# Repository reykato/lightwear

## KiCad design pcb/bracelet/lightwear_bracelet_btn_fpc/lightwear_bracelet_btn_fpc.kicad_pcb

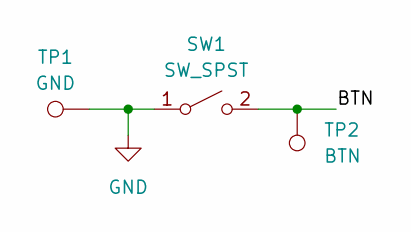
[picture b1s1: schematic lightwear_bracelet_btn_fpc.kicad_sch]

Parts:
SW1: SW_SPST; GT-TC155X-HXXXX-LX
TP1: GND; TestPoint_Pad_1.5x0.8mm_slim
TP2: BTN; TestPoint_Pad_1.5x0.8mm_slim

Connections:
/BTN: SW1.2 (B), TP2.1
GND: SW1.1 (A), TP1.1

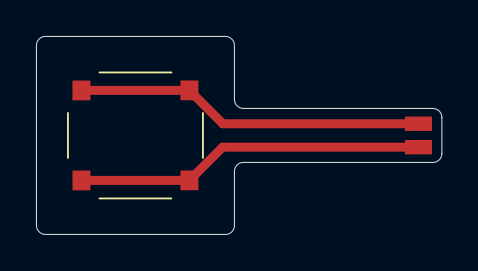
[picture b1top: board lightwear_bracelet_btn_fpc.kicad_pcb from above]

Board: 2 copper layers, 22.5 x 11.0 mm, 3 parts (0 on the bottom side), 2 nets.

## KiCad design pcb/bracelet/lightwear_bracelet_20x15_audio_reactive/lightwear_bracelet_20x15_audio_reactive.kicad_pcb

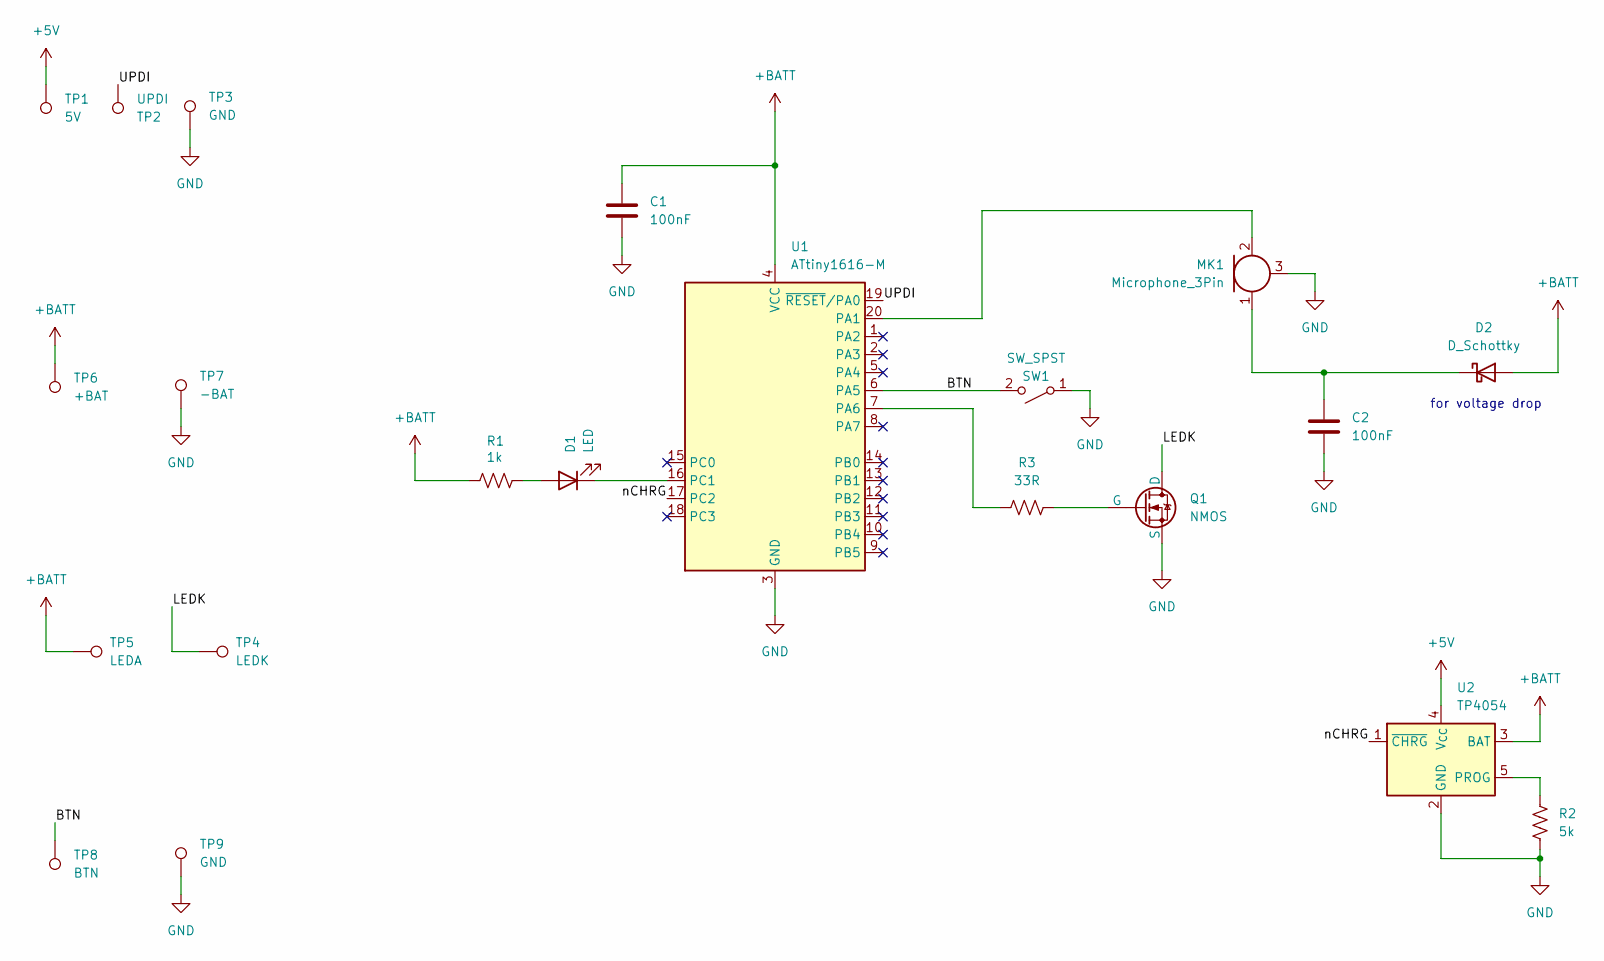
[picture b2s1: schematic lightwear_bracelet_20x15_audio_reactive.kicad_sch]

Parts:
C1, C2: 100nF; C_0402_1005Metric
D1: LED; LED_0603_1608Metric
D2: D_Schottky; SOT-23
MK1: Microphone_3Pin; MSM381ACB026
Q1: NMOS; SOT-23-MOSFET
R1: 1k; R_0402_1005Metric
R2: 5k; R_0402_1005Metric
R3: 33R; R_0402_1005Metric
SW1: SW_SPST; SW4_PTS815 SJM 250 SMTR LFS_CNK
TP1: 5V; TestPoint_Pad_D1.5mm
TP2: UPDI; TestPoint_Pad_D1.5mm
TP3: GND; TestPoint_Pad_D1.5mm
TP4: LEDK; TestPoint_Pad_2.0x1.2mm_slim
TP5: LEDA; TestPoint_Pad_2.0x1.2mm_slim
TP6: +BAT; TestPoint_Pad_Triangle
TP7: -BAT; TestPoint_Pad_Triangle
TP8: BTN; TestPoint_Pad_1.5x0.8mm_slim
TP9: GND; TestPoint_Pad_1.5x0.8mm_slim
U1: ATtiny1616-M; VQFN-20-1EP_3x3mm_P0.4mm_EP1.7x1.7mm
U2: TP4054; TSOT-23-5

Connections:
+5V: TP1.1, U2.4 (V_{CC})
+BATT: C1.1, D2.2 (A), R1.1, TP5.1, TP6.1, U1.4 (VCC), U2.3 (BAT)
/BTN: SW1.2 (B), TP8.1, U1.6 (PA5)
/LEDK: Q1.1 (D), TP4.1
/UPDI: TP2.1, U1.19 (~RESET/PA0)
/nCHRG: U1.17 (PC2), U2.1 (~CHRG)
GND: C1.2, C2.1, MK1.3 (GND), Q1.3 (S), R2.2, SW1.1 (A), TP3.1, TP7.1, TP9.1, U1.3 (GND), U1.21 (GND), U2.2 (GND)
unnamed: D1.2 (A), R1.2
unnamed: D1.1 (K), U1.16 (PC1)
unnamed: C2.2, D2.1 (K), MK1.1 (VDD)
unnamed: MK1.2 (OUT), U1.20 (PA1)
unnamed: Q1.2 (G), R3.2
unnamed: R3.1, U1.7 (PA6)
unnamed: R2.1, U2.5 (PROG)

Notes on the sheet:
for voltage drop

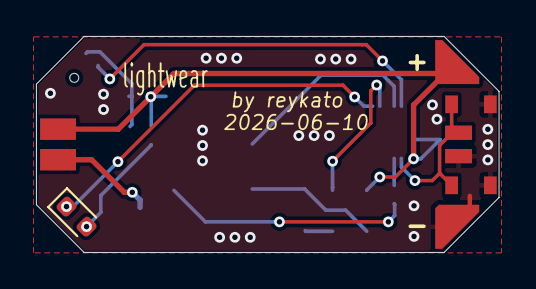
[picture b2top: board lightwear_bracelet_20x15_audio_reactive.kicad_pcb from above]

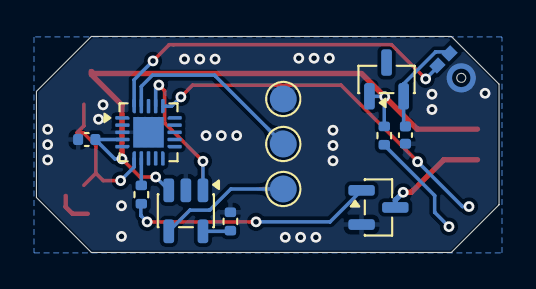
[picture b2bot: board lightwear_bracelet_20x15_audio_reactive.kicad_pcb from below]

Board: 2 copper layers, 25.7 x 12.0 mm, 21 parts (13 on the bottom side), 14 nets.

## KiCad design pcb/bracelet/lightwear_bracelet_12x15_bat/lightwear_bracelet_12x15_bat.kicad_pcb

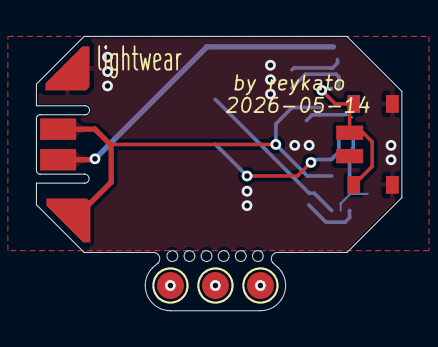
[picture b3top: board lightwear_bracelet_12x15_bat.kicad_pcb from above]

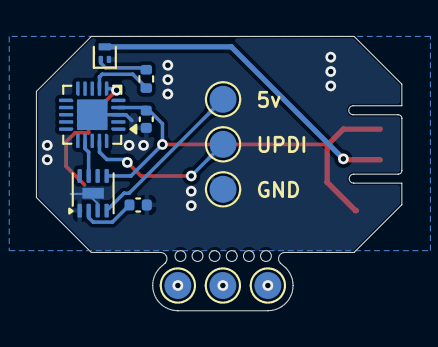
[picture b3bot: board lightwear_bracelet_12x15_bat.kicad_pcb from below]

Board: 2 copper layers, 20.3 x 15.2 mm, 22 parts (12 on the bottom side), 13 nets.

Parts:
C1: 100nF; C_0402_1005Metric
Q1: NMOS; SOT-883
R2: 22k; C_0402_1005Metric
R3: 33R; R_0402_1005Metric
SW1: SW_SPST; SW4_PTS815 SJM 250 SMTR LFS_CNK
TP1, TP2, TP3, TP4#2, TP5#2, TP6#2: TestPoint; TestPoint_Pad_D1.5mm
TP1#2: 5V; TestPoint_Pad_D1.5mm
TP2#2: UPDI; TestPoint_Pad_D1.5mm
TP3#2: GND; TestPoint_Pad_D1.5mm
TP4: LEDK; TestPoint_Pad_2.0x1.2mm_slim
TP5: LEDA; TestPoint_Pad_2.0x1.2mm_slim
TP6: +BAT; TestPoint_Pad_Triangle
TP7: -BAT; TestPoint_Pad_Triangle
TP8: BTN; TestPoint_Pad_1.5x0.8mm_slim
TP9: GND; TestPoint_Pad_1.5x0.8mm_slim
U1: ATtiny1616-M; VQFN-20-1EP_3x3mm_P0.4mm_EP1.7x1.7mm
U2: WB6058D; DFN-8-1EP_2x2mm_P0.5mm_EP0.6x1.2mm

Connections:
+5V: TP1#2.1, U2.4 (V_{CC})
+BATT: C1.1, TP5.1, TP6.1, U1.4 (VCC), U2.5 (BAT)
/BTN: SW1.2 (B), TP8.1, U1.6 (PA5)
/LEDK: Q1.3 (D), TP4.1
/UPDI: TP2#2.1, U1.19 (~RESET/PA0)
/nCHRG: U1.17 (PC2), U2.7 (~CHRG)
GND: C1.2, Q1.2 (S), R2.1, SW1.1 (A), TP3#2.1, TP7.1, TP9.1, U1.3 (GND), U1.21 (GND), U2.1 (TEMP), U2.3 (GND), U2.9 (BASE)
unnamed: Q1.1 (G), R3.2
unnamed: TP1.1, TP6#2.1
unnamed: TP2.1, TP5#2.1
unnamed: TP3.1, TP4#2.1
unnamed: R3.1, U1.7 (PA6)
unnamed: R2.2, U2.2 (ISET)

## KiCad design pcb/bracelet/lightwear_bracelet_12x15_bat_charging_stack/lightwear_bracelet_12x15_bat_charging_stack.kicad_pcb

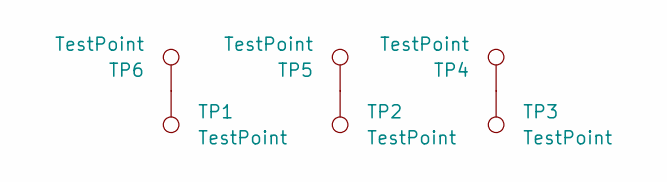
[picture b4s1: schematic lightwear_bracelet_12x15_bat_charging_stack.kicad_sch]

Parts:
TP1, TP2, TP3, TP4, TP5, TP6: TestPoint; TestPoint_Pad_D1.5mm

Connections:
unnamed: TP1.1, TP6.1
unnamed: TP2.1, TP5.1
unnamed: TP3.1, TP4.1

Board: 6 copper layers, 6 parts (3 on the bottom side), 3 nets, no tracks yet.

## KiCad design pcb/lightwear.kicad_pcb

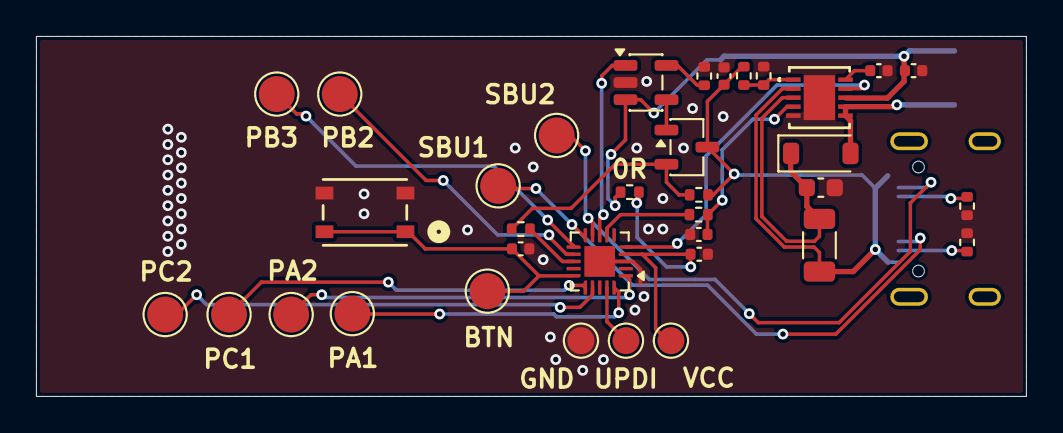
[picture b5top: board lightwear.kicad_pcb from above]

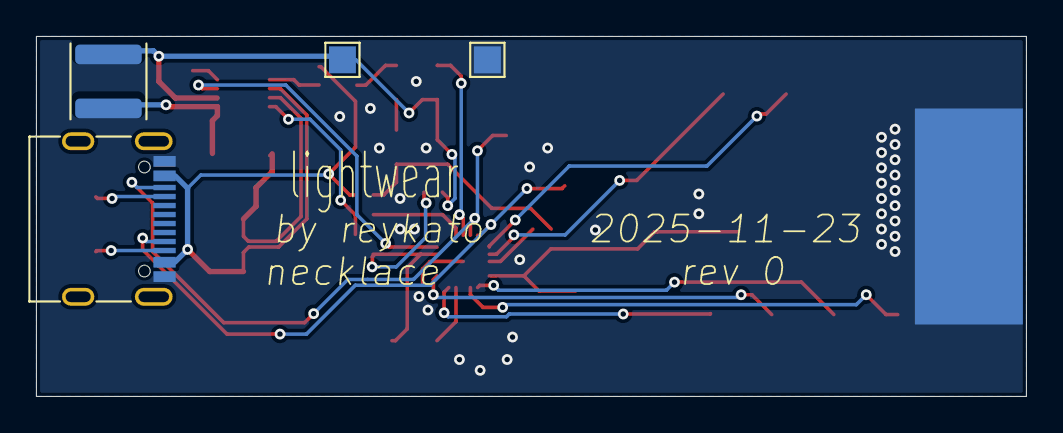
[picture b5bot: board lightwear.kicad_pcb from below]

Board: 2 copper layers, 55.0 x 20.0 mm, 40 parts (5 on the bottom side), 28 nets.

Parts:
C1, C4: 100nF; C_0402_1005Metric
C2: 1uF 35V; C_0603_1608Metric
C5: 2.2uF; C_0402_1005Metric
C6: 470nF; C_0402_1005Metric
C7: 4.7uF; C_0402_1005Metric
C8: 1uF 30V; C_0402_1005Metric
D1: D_Schottky 30V; D_SOD-123
J1: USB_C_Receptacle_USB2.0_16P; USB_C_Receptacle_G-Switch_GT-USB-7010ASV
L1: 4.7uH; L_Changjiang_FNR4030S
Q1: PMOS; SOT-23-3
R1: 33R; R_0402_1005Metric
R3, R4, R11: 5.1k; R_0402_1005Metric
R6: 0.05R; R_1206_3216Metric
R7: 100k 30V; R_0402_1005Metric
R8: 2k; R_0402_1005Metric
R9: 0R; R_0402_1005Metric
R10: 200k 30V; R_0402_1005Metric
R12: 10k 30V; R_0402_1005Metric
SW1: SW_SPST; SW4_PTS815 SJM 250 SMTR LFS_CNK
TP1: USB_SBU1; TestPoint_Pad_D2.0mm
TP2: BTN; TestPoint_Pad_D2.0mm
TP3: MCU_VCC; TestPoint_Pad_D1.5mm
TP4: UPDI; TestPoint_Pad_D1.5mm
TP5: GND; TestPoint_Pad_D1.5mm
TP6: +BATT; TestPoint_Pad_1.5x1.5mm
TP7: GND; TestPoint_Pad_1.5x1.5mm
TP8: PA1; TestPoint_Pad_D2.0mm
TP9: LEDK; TestPoint_Pad_6.0x12.0mm
TP10: PA2; TestPoint_Pad_D2.0mm
TP11: PB2; TestPoint_Pad_D2.0mm
TP12: PB3; TestPoint_Pad_D2.0mm
TP13: PC1; TestPoint_Pad_D2.0mm
TP14: PC2; TestPoint_Pad_D2.0mm
TP16: USB_SBU2; TestPoint_Pad_D2.0mm
U1: LT1618EDD-PBF; DFN-10_DD_LIT
U2: MCP73831-2-OT; SOT-23-5
U3: ATtiny1616-M; VQFN-20-1EP_3x3mm_P0.4mm_EP1.7x1.7mm

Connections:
+BATT: C7.1, L1.2, R9.1, TP6.1, U1.8 (VIN), U2.3 (V_{BAT})
/charger/CHG_GATE: Q1.2 (G), R1.2, R7.1
/charger/CHG_STAT: U2.1 (STAT), U3.8 (PA7)
/charger/VBUS: C8.1, J1.A4 (VBUS), J1.A9 (VBUS), J1.B4 (VBUS), J1.B9 (VBUS), Q1.3 (S), R6.2, R7.2, R10.2, U1.2 (ISN)
/led_driver/FB: R10.1, R12.2, U1.1 (FB)
/led_driver/IADJ: R11.1, U3.7 (PA6)
/led_driver/IADJ_DRV: C4.1, R11.2, U1.4 (IADJ)
/led_driver/nSHDN: U1.9 (*SHDN), U3.5 (PA4)
/mcu/BTN: C6.1, SW1.1 (A), TP2.1, U3.15 (PC0)
/mcu/CHG_GATE: R1.1, U3.13 (PB1)
/mcu/MCU_VCC: C5.2, R9.2, TP3.1, U3.4 (VCC)
/mcu/PA1: TP8.1, U3.20 (PA1)
/mcu/PA2: TP10.1, U3.1 (PA2)
/mcu/PB2: TP11.1, U3.12 (PB2)
/mcu/PB3: TP12.1, U3.11 (PB3)
/mcu/PC1: TP13.1, U3.16 (PC1)
/mcu/PC2: TP14.1, U3.17 (PC2)
/mcu/UPDI: TP4.1, U3.19 (~RESET/PA0)
/mcu/USB_SBU1: J1.A8 (SBU1), TP1.1, U3.10 (PB4)
/mcu/USB_SBU2: J1.B8 (SBU2), TP16.1, U3.9 (PB5)
GND: C1.2, C2.2, C4.2, C5.1, C6.2, C7.2, C8.2, J1.A1 (GND), J1.A12 (GND), J1.B1 (GND), J1.B12 (GND), R3.2, R4.2, R8.1, R12.1, SW1.2 (B), TP5.1, TP7.1, TP9.1, U1.5 (GND), U1.11 (EPAD), U2.2 (V_{SS}), U3.3 (GND), U3.21 (GND)
unnamed: D1.2 (A), L1.1, U1.6 (SW), U1.7 (SW)
unnamed: C2.1, D1.1 (K), R6.1, U1.3 (ISP)
unnamed: J1.A5 (CC1), R3.1
unnamed: J1.B5 (CC2), R4.1
unnamed: Q1.1 (D), U2.4 (V_{DD})
unnamed: C1.1, U1.10 (VC)
unnamed: R8.2, U2.5 (PROG)

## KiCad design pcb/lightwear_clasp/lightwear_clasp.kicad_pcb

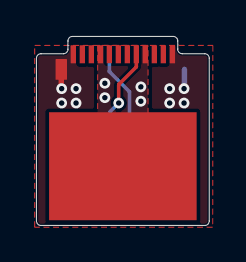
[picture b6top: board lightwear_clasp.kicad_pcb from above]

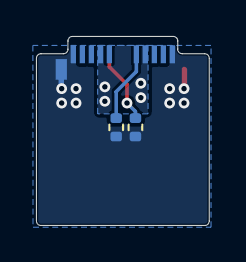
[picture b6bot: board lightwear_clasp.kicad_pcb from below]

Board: 2 copper layers, 9.6 x 10.5 mm, 4 parts (2 on the bottom side), 4 nets.

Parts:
J1: 1054440001; MOLEX_1054440001
R1, R2: 5.1k; R_0402_1005Metric
TP1: LEDA; TestPoint_Pad_6.0x8.2mm

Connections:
GND: J1.A1 (GND_A1), J1.A12 (GND_A12), J1.B1 (GND_B1), J1.B12 (GND_B12), J1.SH1 (SHIELD1), J1.SH2 (SHIELD2), R1.2, R2.2
unnamed: J1.A8 (SBU1), R1.1
unnamed: J1.B8 (SBU2), R2.1
VBUS: J1.A4 (VBUS_A4), J1.A9 (VBUS_A9), J1.B4 (VBUS_B4), J1.B9 (VBUS_B9), TP1.1

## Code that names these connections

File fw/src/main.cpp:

#include <Arduino.h>

// Pin definitions
#define DRV_nSHDN PIN_PA4  // PA4
#define ISET PIN_PA6       // PA6
#define USB_SBU1 PIN_PB4   // PB4
#define USB_SBU2 PIN_PB5   // PB5
#define BTN PIN_PC0        // PC0
#define LED_OFF PIN_PC2
#define LED_LOW PIN_PC1
#define LED_MED PIN_PA2
#define LED_HIGH PIN_PA1

// Modes
enum Mode { MODE_OFF, MODE_LOW, MODE_MED, MODE_HIGH };
Mode currentMode = MODE_OFF;

// Debouncing variables
unsigned long lastDebounceTime = 0;
const unsigned long debounceDelay = 50;
bool lastBtnState = HIGH;
bool btnState = HIGH;

// Dithering variables (for fractional step between two adjacent 8-bit DAC values)
// Using the existing RC filter (4.7k + 100nF) the output will be the time-average
// of the DAC toggles between `low` and `high` values.
static float dith_acc = 0.0f;
static unsigned long lastToggleMicros = 0;
// Toggle period in microseconds (200us -> 5 kHz). Tune as needed.
static const unsigned long togglePeriodUs = 200UL;
// Desired effective 8-bit DAC value for the LOW mode. Set fractional part here.
// E.g. 170.37 will produce an average between 170 and 171.
static float desired_low_mode_value = 170.6f;

void dac_init() {
    // 1. Configure PA6 as output
    PORTA.DIRSET = PIN6_bm;

    // Set VREF = VDD (raw bits 0x3)
    VREF.CTRLA = (VREF.CTRLA & ~0x07) | 0x02; // clear DAC0REFSEL bits, set to 0x2

    // 2. Enable DAC0, enable output pin
    DAC0.CTRLA = DAC_ENABLE_bm | DAC_OUTEN_bm;

    // 3. Start with 0V
    DAC0.DATA = 0;
}

void dac_set_voltage(uint8_t value) {
    // 8-bit value: 0 = 0V, 255 = VREF
    DAC0.DATA = value;
}

// Non-blocking dither update: toggles between `low` and `high` based on fractional
// part of `desired`. Call frequently from `loop()`.
void dither_update(float desired, uint8_t low, uint8_t high) {
    unsigned long now = micros();
    if ((unsigned long)(now - lastToggleMicros) < togglePeriodUs) return;
    lastToggleMicros = now;

    float frac = desired - (float)low;
    if (frac <= 0.0f) {
        // always low
        dith_acc = 0.0f;
        dac_set_voltage(low);
        return;
    }
    if (frac >= 1.0f) {
        // always high
        dith_acc = 0.0f;
        dac_set_voltage(high);
        return;
    }

    dith_acc += frac;
    if (dith_acc >= 1.0f) {
        dith_acc -= 1.0f;
        dac_set_voltage(high);
    } else {
        dac_set_voltage(low);
    }
}

void setup() {
    // Configure pins
    pinMode(DRV_nSHDN, INPUT_PULLUP);  // Start with pull-up (high)
    pinMode(USB_SBU1, INPUT_PULLUP);
    pinMode(USB_SBU2, INPUT_PULLUP);
    pinMode(BTN, INPUT_PULLUP);
    pinMode(LED_OFF, OUTPUT);
    pinMode(LED_LOW, OUTPUT);
    pinMode(LED_MED, OUTPUT);
    pinMode(LED_HIGH, OUTPUT);
    dac_init();
}

void loop() {
    // Read USB signals
    bool usbHigh = (digitalRead(USB_SBU1) == HIGH) && (digitalRead(USB_SBU2) == HIGH);

    // Debounce button
    bool reading = digitalRead(BTN);
    if (reading != lastBtnState) {
        lastDebounceTime = millis();
    }
    if ((millis() - lastDebounceTime) > debounceDelay) {
        if (reading != btnState) {
            btnState = reading;
            if (btnState == LOW) {  // Button pressed (active low)
                currentMode = (Mode)((currentMode + 1) % 4);
            }
        }
    }
    lastBtnState = reading;

    // Set mode indicators
    digitalWrite(LED_OFF, currentMode == MODE_OFF ? HIGH : LOW);
    digitalWrite(LED_LOW, currentMode == MODE_LOW ? HIGH : LOW);
    digitalWrite(LED_MED, currentMode == MODE_MED ? HIGH : LOW);
    digitalWrite(LED_HIGH, currentMode == MODE_HIGH ? HIGH : LOW);

    // Control DRV_nSHDN
    if (usbHigh || currentMode == MODE_OFF) {
        pinMode(DRV_nSHDN, OUTPUT);
        digitalWrite(DRV_nSHDN, LOW);
    } else {
        pinMode(DRV_nSHDN, INPUT_PULLUP);  // Release to high
    }

    // Control ISET (use dithering in LOW mode to synthesize fractional 8-bit values)
    uint16_t duty = 255;
    switch (currentMode) {
        case MODE_OFF:
            duty = 255; // DRV disabled / max
            // no dithering, hold high
            dac_set_voltage((uint8_t)duty);
            break;
        case MODE_LOW:
            // Use dithering between 170 and 171 to synthesize fractional values.
            // Set `desired_low_mode_value` above to change the exact fractional target.
            dither_update(desired_low_mode_value, 170u, 171u);
            break;
        case MODE_MED:
            duty = 168;
            dac_set_voltage((uint8_t)duty);
            break;
        case MODE_HIGH:
            duty = 165;
            dac_set_voltage((uint8_t)duty);
            break;
    }

    // Small non-blocking wait to avoid burning CPU; dithering timing uses micros().
    delayMicroseconds(50);
}

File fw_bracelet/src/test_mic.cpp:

/*
 * ATtiny1616 Mic -> LED Brightness Pipeline (v1, amplitude-only, no FFT)
 * --------------------------------------------------------------------
 * Goal: confirm the full signal chain works end-to-end --
 *   mic -> ADC -> DC removal -> AGC -> brightness mapping -> DAC -> strip
 *
 * This intentionally skips frequency analysis. It just reacts to overall
 * loudness, using a windowed peak-to-brightness mapping. Once this is
 * confirmed working on the bench, the FFT/band-splitting stage can be
 * inserted between AGC and brightness mapping.
 *
 * Board: ATtiny1616 (megaTinyCore)
 * Tools > Chip: ATtiny1616
 * Tools > Clock: 20MHz internal
 *
 * WIRING ASSUMPTION:
 *   - Mic module output -> PA4 (ADC0 AIN4) -- change ADC_PIN/MUXPOS if different
 *   - Mic module biased to ~VCC/2 (typical electret breakout w/ opamp)
 *   - dacSetVoltage(float) already implemented elsewhere, drives strip dimming
 */

#include <Arduino.h>

#define PIN_LED   PIN_PC1
#define PIN_nCHRG PIN_PC2
#define PIN_BTN   PIN_PA5
#define PIN_GATE  PIN_PA6 // (DAC output)


// ---------- Configuration ----------
#define ADC_PIN           PIN_PA1   // change to match your mic input pin
#define SAMPLE_WINDOW_MS  20        // how often we update brightness (ms) -- ~50Hz update rate

// AGC tuning
#define AGC_TARGET        400       // target peak amplitude (post-DC-removal, ADC counts)
#define AGC_MIN_GAIN      1         // gain stored as fixed point Q4 (i.e. divide by 16 later)
#define AGC_MAX_GAIN      255       // max ~16x gain in Q4
#define AGC_DECAY_SHIFT   7         // how fast AGC peak tracker decays (higher = slower)

// DC offset tracker tuning
#define DC_SHIFT          6         // running average shift factor (higher = slower/smoother)

// Brightness smoothing (decay) -- prevents flicker, gives a falling "tail"
#define BRIGHTNESS_ATTACK_SHIFT  1  // how fast brightness rises to a new peak (lower = faster)
#define BRIGHTNESS_DECAY_SHIFT   4  // how fast brightness falls after a peak (higher = slower)

// DAC output voltage range
#define DAC_VOLTAGE_MIN   1.2f
#define DAC_VOLTAGE_MAX   1.70f

// DAC resolution used by the ATtiny1616 DAC (8-bit)
#define DAC_MAX 255u


// ---------- Global state ----------
static int16_t  dcOffset       = 512;  // running DC offset estimate, init to expected mid-rail
static uint16_t agcPeak        = 1;    // running peak estimate used by AGC, avoid 0 (div by zero)
static uint8_t  agcGainQ4      = 16;   // current AGC gain in Q4 fixed point (16 = 1.0x)
static uint16_t windowPeak     = 0;    // peak seen during the current brightness update window
static float    smoothedLevel  = 0.0f; // smoothed 0.0-1.0 brightness level

static void configurePins(void) {
  pinMode(PIN_LED, OUTPUT);
  digitalWrite(PIN_LED, LOW);
  pinMode(PIN_nCHRG, INPUT_PULLUP);
  pinMode(PIN_BTN, INPUT_PULLUP);
}

// Setup DAC if available
static void setupDAC(void) {
		VREF.CTRLA = VREF.CTRLA | VREF_DAC0REFSEL_2V5_gc;

    // Configure PA6 as output
    PORTA.DIRSET = PIN6_bm;

    // Enable DAC0, enable output pin
    DAC0.CTRLA = DAC_ENABLE_bm | DAC_OUTEN_bm | DAC_RUNSTDBY_bm;

    // Start with 0V
    DAC0.DATA = 0;
}

// Convert desired voltage as float (0..2.5V) to 8-bit number
static inline uint8_t voltageToDac(float v) {
  if (v <= 0.0f) return 0;
  if (v >= 2.5f) return (uint8_t)DAC_MAX;
  return (uint8_t)((v / 2.5f) * (float)DAC_MAX + 0.5f);
}

static inline void dacSetVoltage(float voltage) {
  DAC0.DATA = voltageToDac(voltage);
}

// ---------- ADC Setup ----------
void setupADC() {
	pinMode(ADC_PIN, INPUT);
	PORTA.PIN4CTRL = PORT_ISC_INPUT_DISABLE_gc;

  ADC0.CTRLC = ADC_PRESC_DIV16_gc | ADC_REFSEL_VDDREF_gc;
  ADC0.CTRLA = ADC_RESSEL_10BIT_gc | ADC_ENABLE_bm;
  ADC0.CTRLB = ADC_SAMPNUM_ACC16_gc;   // 16x hardware oversampling
  ADC0.SAMPCTRL = 14;
  ADC0.MUXPOS = ADC_MUXPOS_AIN1_gc;    // <-- update to match ADC_PIN
}

uint16_t readADC() {
  ADC0.COMMAND = ADC_STCONV_bm;
  while (!(ADC0.INTFLAGS & ADC_RESRDY_bm));
  uint16_t raw = ADC0.RES;
  ADC0.INTFLAGS = ADC_RESRDY_bm;
  return raw >> 4; // rescale 16x-accumulated sum back to ~10-bit range
}

// ---------- DC Offset Removal ----------
int16_t removeDC(uint16_t sample) {
  dcOffset += ((int16_t)sample - dcOffset) >> DC_SHIFT;
  return (int16_t)sample - dcOffset;
}

// ---------- AGC ----------
int16_t applyAGC(int16_t acSample) {
  uint16_t absSample = (acSample < 0) ? -acSample : acSample;

  if (absSample > agcPeak) {
    agcPeak = absSample;
  } else {
    agcPeak -= (agcPeak >> AGC_DECAY_SHIFT);
    if (agcPeak < 1) agcPeak = 1;
  }

  uint32_t desiredGainQ4 = ((uint32_t)AGC_TARGET * 16) / agcPeak;
  if (desiredGainQ4 > AGC_MAX_GAIN) desiredGainQ4 = AGC_MAX_GAIN;
  if (desiredGainQ4 < AGC_MIN_GAIN) desiredGainQ4 = AGC_MIN_GAIN;

  agcGainQ4 = agcGainQ4 + (((int16_t)desiredGainQ4 - (int16_t)agcGainQ4) >> 2);

  int32_t gained = ((int32_t)acSample * agcGainQ4) >> 4;
  if (gained > 32767) gained = 32767;
  if (gained < -32768) gained = -32768;

  return (int16_t)gained;
}

// ---------- Brightness Mapping ----------

// Maps a normalized 0.0-1.0 level to the configured DAC voltage range and
// sends it out. Kept separate so you can swap in gamma correction later.
void setLEDBrightness(float level) {
  if (level < 0.0f) level = 0.0f;
  if (level > 1.0f) level = 1.0f;

  float voltage = DAC_VOLTAGE_MIN + level * (DAC_VOLTAGE_MAX - DAC_VOLTAGE_MIN);
  dacSetVoltage(voltage);
}

// Converts the AGC'd peak-amplitude reading for this window into a
// smoothed 0.0-1.0 brightness level with fast attack / slow decay,
// then drives the DAC.
void updateBrightnessFromPeak(uint16_t peak) {
  // Normalize peak (post-AGC, so it should roughly track AGC_TARGET as "full scale")
  float target = (float)peak / (float)AGC_TARGET;
  if (target > 1.0f) target = 1.0f;

  if (target > smoothedLevel) {
    // Rise quickly toward new peak
    smoothedLevel += (target - smoothedLevel) / (1 << BRIGHTNESS_ATTACK_SHIFT);
  } else {
    // Fall slowly for a smooth trailing decay
    smoothedLevel += (target - smoothedLevel) / (1 << BRIGHTNESS_DECAY_SHIFT);
  }

  setLEDBrightness(smoothedLevel);
}

// ---------- Main Loop ----------
unsigned long windowStart = 0;

// void loop() {
//   uint16_t rawADC    = readADC();
//   int16_t  dcRemoved = removeDC(rawADC);
//   int16_t  agcSample = applyAGC(dcRemoved);

//   uint16_t absAGC = (agcSample < 0) ? -agcSample : agcSample;
//   if (absAGC > windowPeak) windowPeak = absAGC;

//   if (millis() - windowStart >= SAMPLE_WINDOW_MS) {
//     windowStart = millis();
//     updateBrightnessFromPeak(windowPeak);
//     windowPeak = 0;
//   }

//   // No delay -- sample as fast as practical within each window
// }

uint16_t restingRaw = 0;

void setup() {
	configurePins();
  setupADC();
  setupDAC();
  setLEDBrightness(1.0f);
	delay(200);
	setLEDBrightness(0.0f);
	delay(200);
	digitalWrite(PIN_LED, LOW);
	delay(200);
	digitalWrite(PIN_LED, HIGH);
	delay(200);
	digitalWrite(PIN_LED, LOW);


  // Average several readings at startup (assumes mic is quiet at power-on)
  uint32_t sum = 0;
  for (int i = 0; i < 32; i++) {
    sum += readADC();
    delay(2);
  }
  restingRaw = sum / 32;
}

void loop() {
  uint16_t raw = readADC();
  int16_t deviation = (int16_t)raw - (int16_t)restingRaw;

  // Scale deviation to brightness -- adjust SENSITIVITY to taste
  const float SENSITIVITY = 8.0f; // try 4-20, higher = more amplified
  float level = 0.5f + (deviation / 1023.0f) * SENSITIVITY;

  setLEDBrightness(level);
}

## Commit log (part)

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2025-11-24 rev0 done
2025-11-24 small tweak
2025-11-24 finishing touches made, exported as rev0
2025-11-24 added lightwear_clasp pcb, male usb-c
2025-11-24 generated gerbers
2025-11-24 updated 3d models
2025-12-13 bracelet rev0 complete
2025-12-14 rev0 of bracelet pcb finished and ordered
2025-12-30 firmware working for bracelet
2026-01-01 change vref to 2.5v
2026-01-01 standby sleep working
2026-02-02 Started work on PCB without battery chips
2026-02-11 15x20mm battery version done
2026-02-15 changed battery connection to interface with bms board directly
2026-03-08 code for bracelet working. 4 brightness modes (including OFF) and battery checking (25% increments)
2026-03-08 correct GATE_V_HIGH
2026-03-09 fix ADC setup and battery measurement, improve showBatteryLevel with delays before and after showing battery level
2026-03-31 refactor: improve power management and ADC configuration, enhance battery level indication
2026-03-31 docs: add detailed measurements and observations on power consumption and sleep mode performance
2026-04-15 12x15 bat finished
2026-05-07 fix footprint for sot-883 mosfet, add pads for flex button board
2026-06-03 12x15 bat PCB fixed with rev2 in code: removed references to onboard LED, restrict to only OFF, LOW, HIGH modes
2026-06-30 20x15_audio_reactive rev0 done
